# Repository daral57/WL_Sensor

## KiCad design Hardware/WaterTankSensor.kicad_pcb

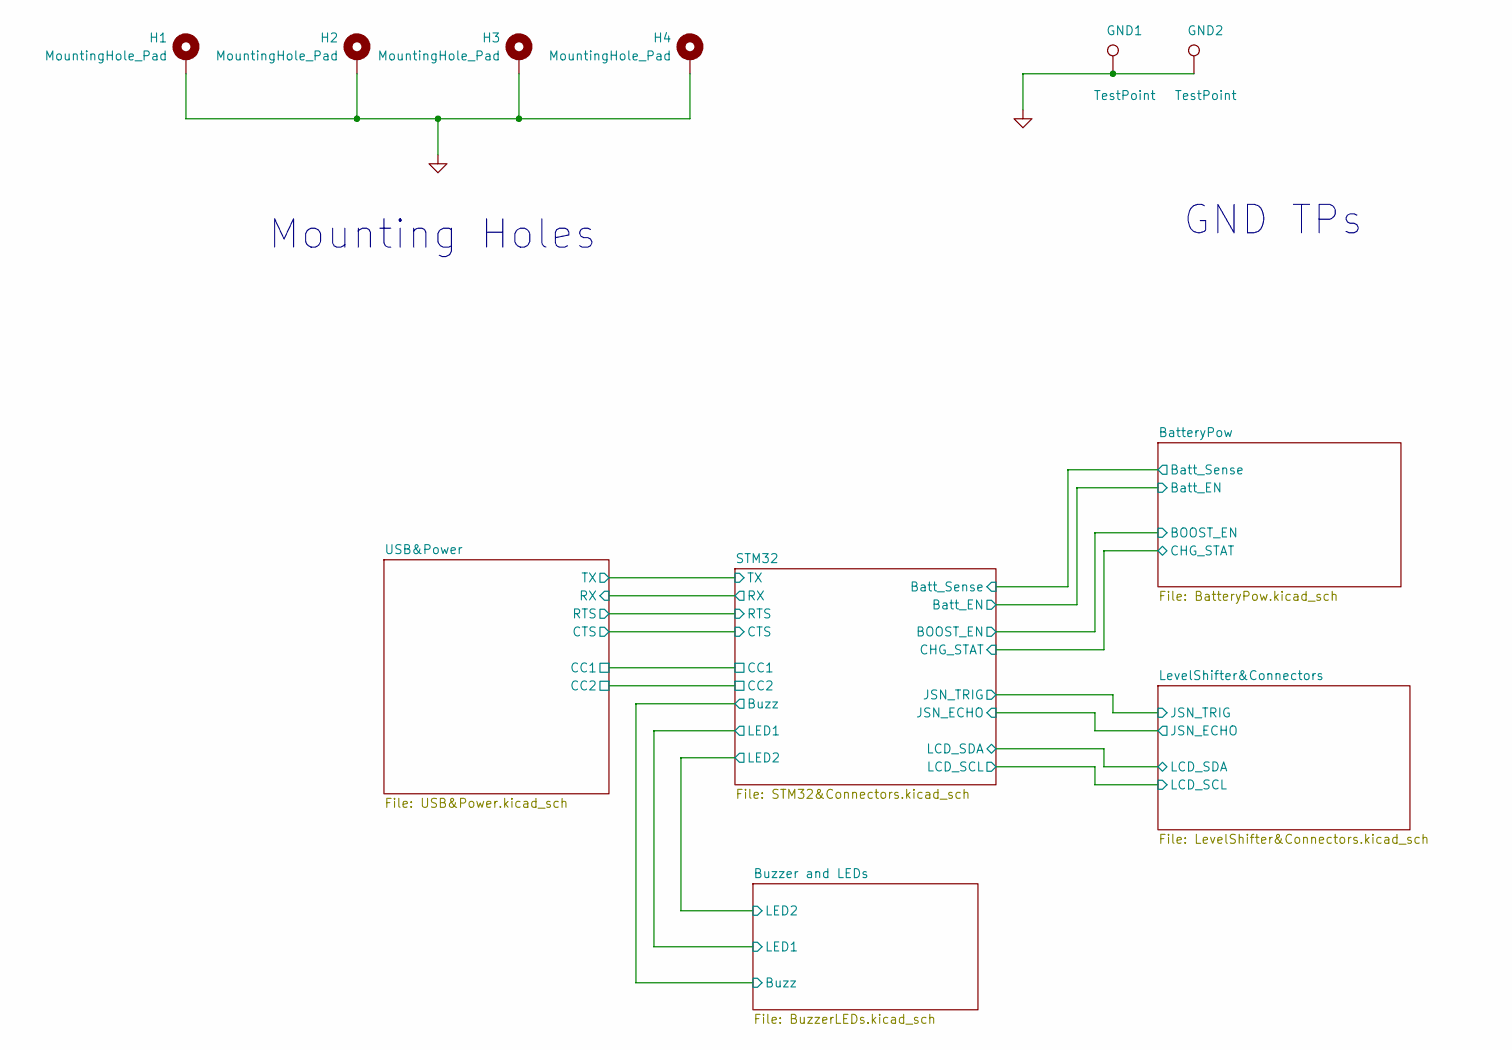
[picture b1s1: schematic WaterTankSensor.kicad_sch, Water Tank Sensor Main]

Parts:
GND1, GND2: TestPoint; TestPoint_Pad_4.0x4.0mm
H1, H2, H3, H4: MountingHole_Pad; MountingHole_3.2mm_M3_Pad_Via

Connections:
GND: GND1.1 (1_1), GND2.1 (1_1), H1.1 (1_1), H2.1 (1_1), H3.1 (1_1), H4.1 (1_1); also elsewhere on the board

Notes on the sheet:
GND TPs
Mounting Holes

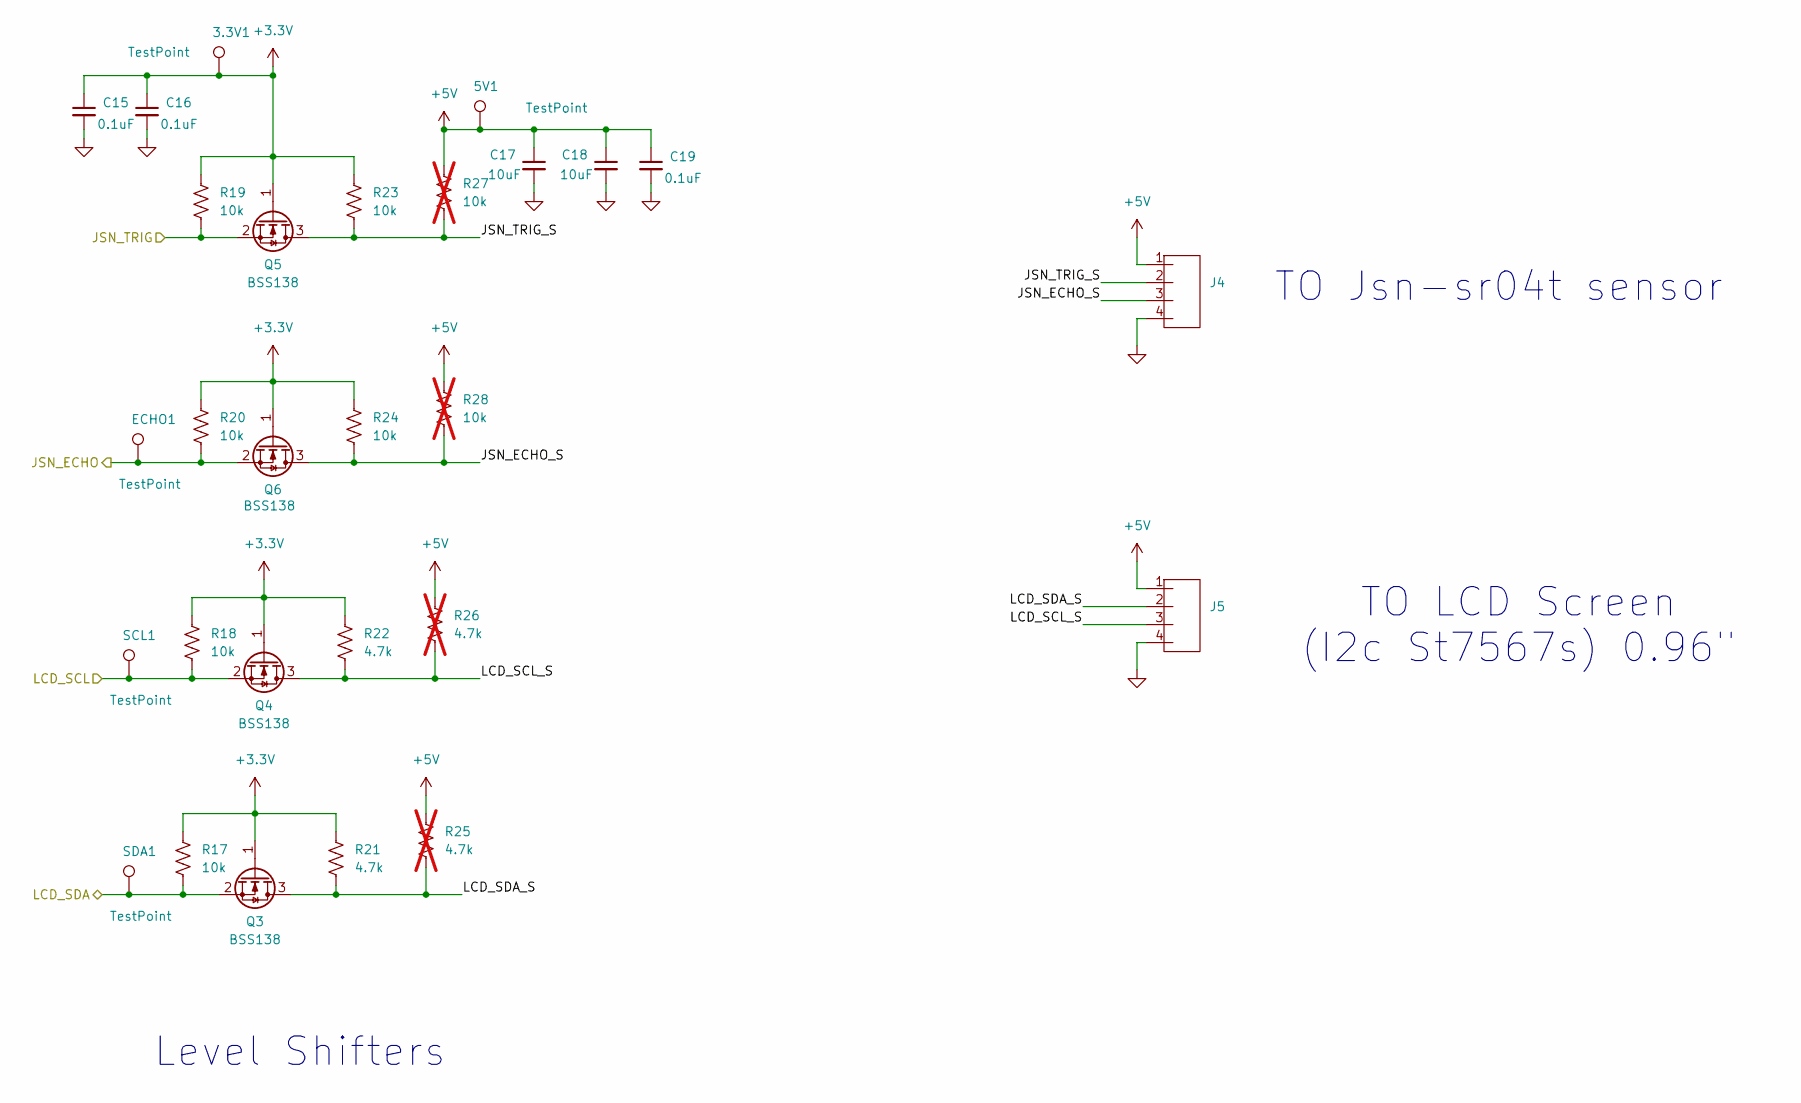
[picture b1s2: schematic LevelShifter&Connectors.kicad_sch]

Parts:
3.3V1, 5V1: TestPoint; TestPoint_Pad_D2.0mm
C15, C16, C19: 0.1uF; C_0603_1608Metric_Pad1.08x0.95mm_HandSolder; MPN CL10B104KO8NNNC
C17, C18: 10uF; C_0603_1608Metric_Pad1.08x0.95mm_HandSolder; MPN CL10B106MQ8NRNC
ECHO1: TestPoint; TestPoint_Pad_D2.0mm
J4, J5: CONN4_A2-4PA-2.54DSA71_HIR; MPN A2-4PA-2.54DSA(71)
Q3, Q4, Q5, Q6: BSS138; SOT-23; MPN BSS138
R17, R18, R19, R20, R23, R24: 10k; R_0603_1608Metric_Pad0.98x0.95mm_HandSolder; MPN CRCW060310K0FKEAHP
R21, R22: 4.7k; R_0603_1608Metric_Pad0.98x0.95mm_HandSolder; MPN CRCW06034K70FKEAHP
R25, R26: 4.7k; R_0603_1608Metric_Pad0.98x0.95mm_HandSolder; MPN CRCW06034K70FKEAHP; not fitted
R27, R28: 10k; R_0603_1608Metric_Pad0.98x0.95mm_HandSolder; MPN CRCW060310K0FKEAHP; not fitted
SCL1: TestPoint; TestPoint_Pad_D2.0mm
SDA1: TestPoint; TestPoint_Pad_D2.0mm

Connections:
+3.3V: 3.3V1.1 (1_1), C15.1, C16.1, Q3.1 (G), Q4.1 (G), Q5.1 (G), Q6.1 (G), R17.2, R18.2, R19.2, R20.2, R21.2, R22.2, R23.2, R24.2; also elsewhere on the board
+5V: 5V1.1 (1_1), C17.1, C18.1, C19.1, J4.1, J5.1, R25.2, R26.2, R27.2, R28.2; also elsewhere on the board
/LevelShifter&Connectors/JSN_ECHO: ECHO1.1 (1_1), Q6.2 (S), R20.1; also elsewhere on the board
/LevelShifter&Connectors/JSN_ECHO_S: J4.3, Q6.3 (D), R24.1, R28.1
/LevelShifter&Connectors/JSN_TRIG: Q5.2 (S), R19.1; also elsewhere on the board
/LevelShifter&Connectors/JSN_TRIG_S: J4.2, Q5.3 (D), R23.1, R27.1
/LevelShifter&Connectors/LCD_SCL: Q4.2 (S), R18.1, SCL1.1 (1_1); also elsewhere on the board
/LevelShifter&Connectors/LCD_SCL_S: J5.3, Q4.3 (D), R22.1, R26.1
/LevelShifter&Connectors/LCD_SDA: Q3.2 (S), R17.1, SDA1.1 (1_1); also elsewhere on the board
/LevelShifter&Connectors/LCD_SDA_S: J5.2, Q3.3 (D), R21.1, R25.1
GND: C15.2, C16.2, C17.2, C18.2, C19.2, J4.4, J5.4; also elsewhere on the board

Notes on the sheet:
TO Jsn-sr04t sensor
TO LCD Screen (I2c St7567s) 0.96"
Level Shifters

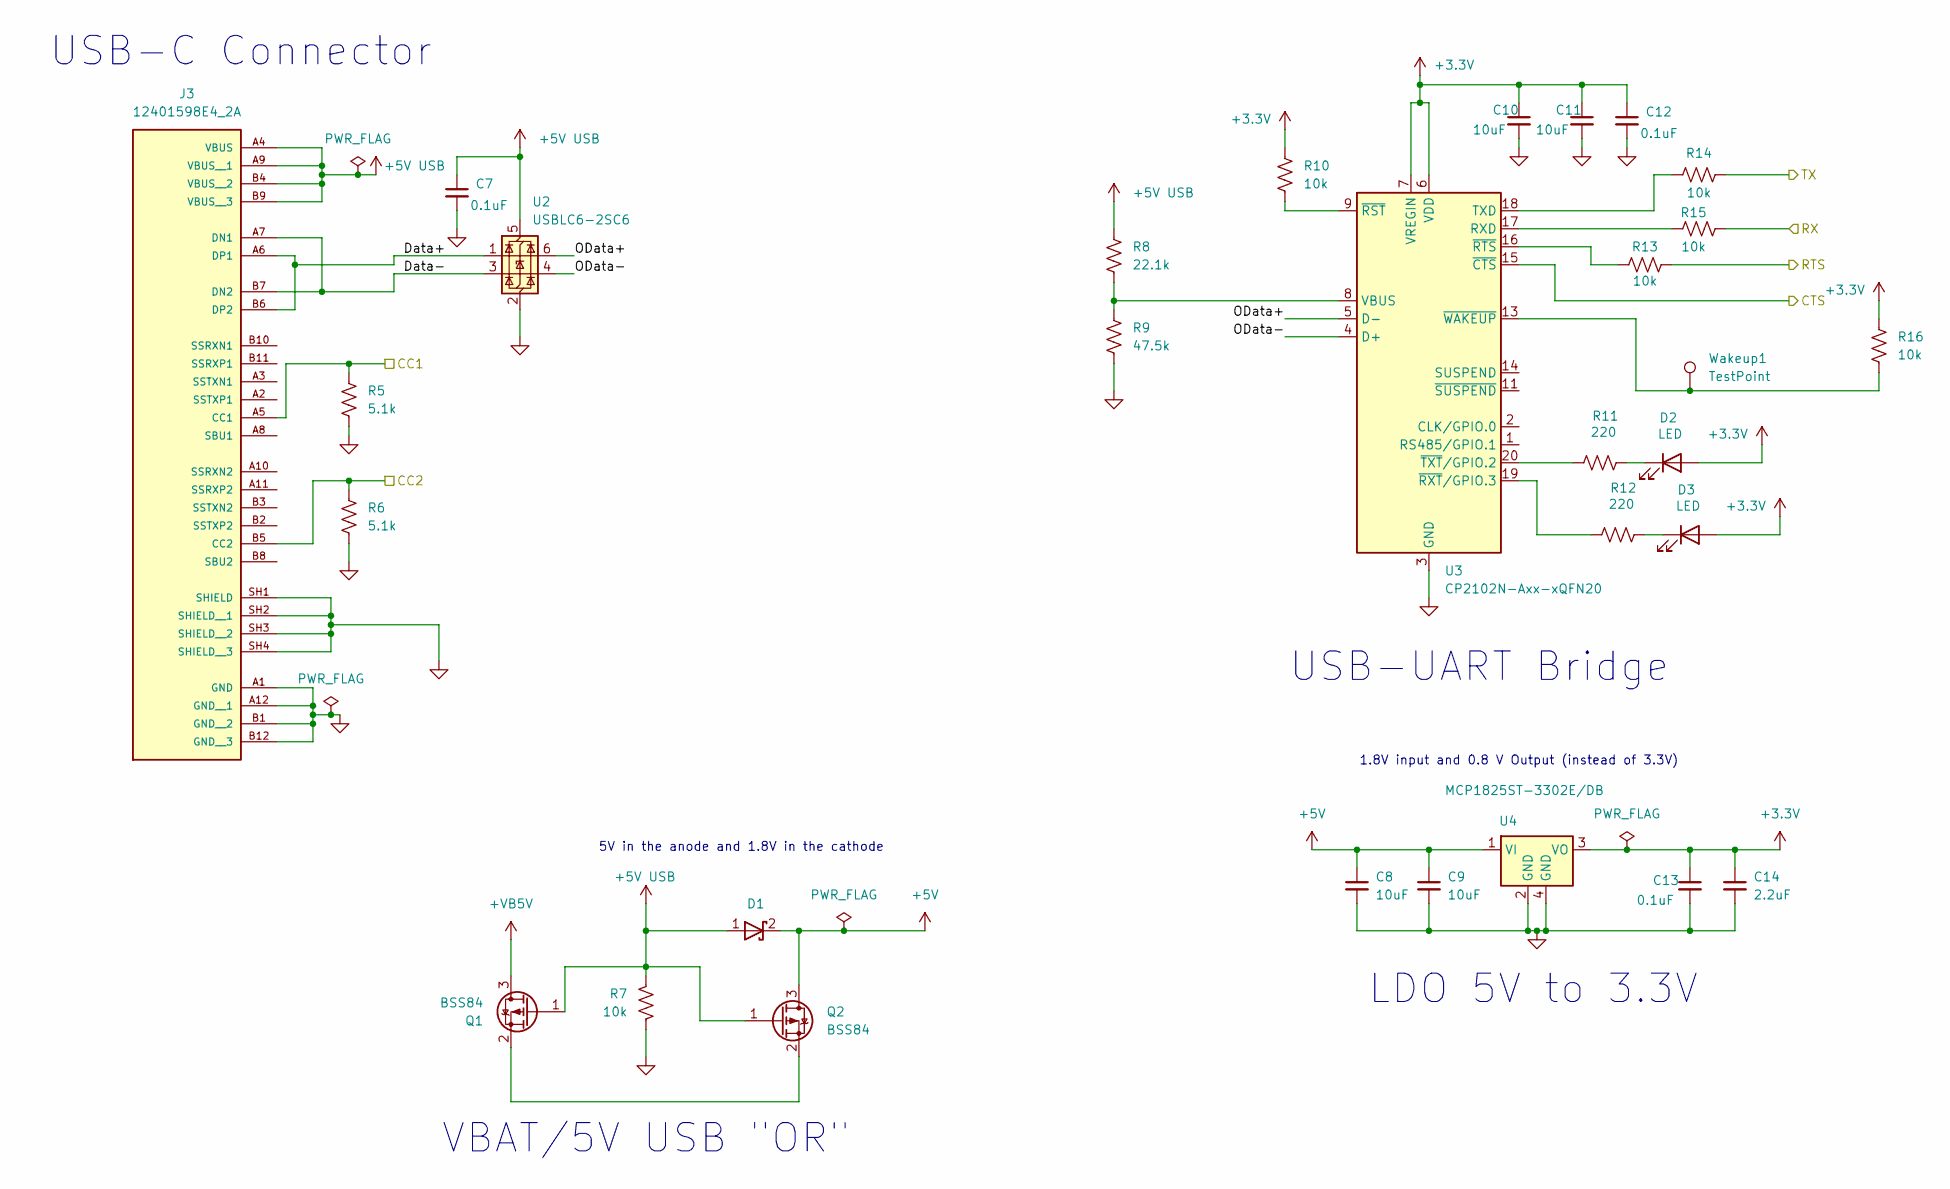
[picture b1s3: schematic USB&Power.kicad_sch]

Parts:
C7, C12, C13: 0.1uF; C_0603_1608Metric_Pad1.08x0.95mm_HandSolder; MPN CL10B104KO8NNNC
C8, C9, C10, C11: 10uF; C_0603_1608Metric_Pad1.08x0.95mm_HandSolder; MPN CL10B106MQ8NRNC
C14: 2.2uF; C_0603_1608Metric_Pad1.08x0.95mm_HandSolder; MPN CL10A225KQ8NNWC
D1: USC_TOS; MPN CUS10S30,H3F
D2, D3: LED; LED_0603_1608Metric; MPN 150060VS75000
J3: 12401598E4_2A; AMPHENOL_12401598E4_2A; PARTREV 4
Q1, Q2: BSS84; SOT-23; MPN BSS84
R5, R6: 5.1k; R_0603_1608Metric_Pad0.98x0.95mm_HandSolder; MPN CRCW0603220RJNEAHP
R7, R10, R13, R15, R16: 10k; R_0603_1608Metric_Pad0.98x0.95mm_HandSolder; MPN CRCW060310K0FKEAHP
R8: 22.1k; R_0603_1608Metric_Pad0.98x0.95mm_HandSolder; MPN CRCW060310K0FKEAHP
R9: 47.5k; R_0603_1608Metric_Pad0.98x0.95mm_HandSolder; MPN CRCW060347K5FKEAHP
R11, R12: 220; R_0603_1608Metric_Pad0.98x0.95mm_HandSolder; MPN CRCW0603220RJNEAHP
R14: 10k; R_0603_1608Metric_Pad0.98x0.95mm_HandSolder; MPN CRCW060322K1FKEAHP
U2: USBLC6-2SC6; SOT-23-6; MPN USBLC6-2SC6
U3: CP2102N-Axx-xQFN20; SiliconLabs_QFN-20-1EP_3x3mm_P0.5mm_EP1.8x1.8mm; MPN CP2102N-A02-GQFN20R
U4: MCP1825ST-3302E/DB; MCP1825ST-3302EDB; MPN MCP1825ST-3302E/DB
Wakeup1: TestPoint; TestPoint_Pad_D2.0mm

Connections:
+3.3V: C10.1, C11.1, C12.1, C13.1, C14.1, D2.2 (A), D3.2 (A), R10.2, R16.2, U3.6 (VDD), U3.7 (VREGIN), U4.3 (VO); also elsewhere on the board
+5V: C8.1, C9.1, D1.2 (K), Q2.3 (D), U4.1 (VI); also elsewhere on the board
+5V USB: C7.1, D1.1 (A), J3.A4 (VBUS), J3.A9 (VBUS__1), J3.B4 (VBUS__2), J3.B9 (VBUS__3), Q1.1 (G), Q2.1 (G), R7.2, R8.1, U2.5 (VBUS); also elsewhere on the board
+VB5V: Q1.3 (D); also elsewhere on the board
/STM32/CC1: J3.A5 (CC1), R5.2; also elsewhere on the board
/STM32/CC2: J3.B5 (CC2), R6.2; also elsewhere on the board
/STM32/NRST: U3.15 (~CTS); also elsewhere on the board
/STM32/RX: R15.1; also elsewhere on the board
/STM32/TCK_SWCLK: R13.1; also elsewhere on the board
/STM32/TX: R14.1; also elsewhere on the board
/USB&Power/Data+: J3.A6 (DP1), J3.B6 (DP2), U2.1 (I/O1)
/USB&Power/Data-: J3.A7 (DN1), J3.B7 (DN2), U2.3 (I/O2)
/USB&Power/OData+: U2.6 (I/O1), U3.5 (D-)
/USB&Power/OData-: U2.4 (I/O2), U3.4 (D+)
GND: C7.2, C8.2, C9.2, C10.2, C11.2, C12.2, C13.2, C14.2, J3.A1 (GND), J3.A12 (GND__1), J3.B1 (GND__2), J3.B12 (GND__3), J3.SH1 (SHIELD), J3.SH2 (SHIELD__1), J3.SH3 (SHIELD__2), J3.SH4 (SHIELD__3), R5.1, R6.1, R7.1, R9.2, U2.2 (GND), U3.3 (GND), U3.12 (GND), U3.21 (GND), U4.2 (GND), U4.4 (GND); also elsewhere on the board
unnamed: D2.1 (K), R11.2
unnamed: D3.1 (K), R12.2
unnamed: Q1.2 (S), Q2.2 (S)
unnamed: R15.2, U3.17 (RXD)
unnamed: R14.2, U3.18 (TXD)
unnamed: R8.2, R9.1, U3.8 (VBUS)
unnamed: R10.1, U3.9 (~RST)
unnamed: R13.2, U3.16 (~RTS)
unnamed: R12.1, U3.19 (~RXT/GPIO.3)
unnamed: R11.1, U3.20 (~TXT/GPIO.2)
unnamed: R16.1, U3.13 (~WAKEUP), Wakeup1.1 (1_1)

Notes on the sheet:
USB-C Connector
VBAT/5V USB "OR"
5V in the anode and 1.8V in the cathode
USB-UART Bridge
LDO 5V to 3.3V
1.8V input and 0.8 V Output (instead of 3.3V)

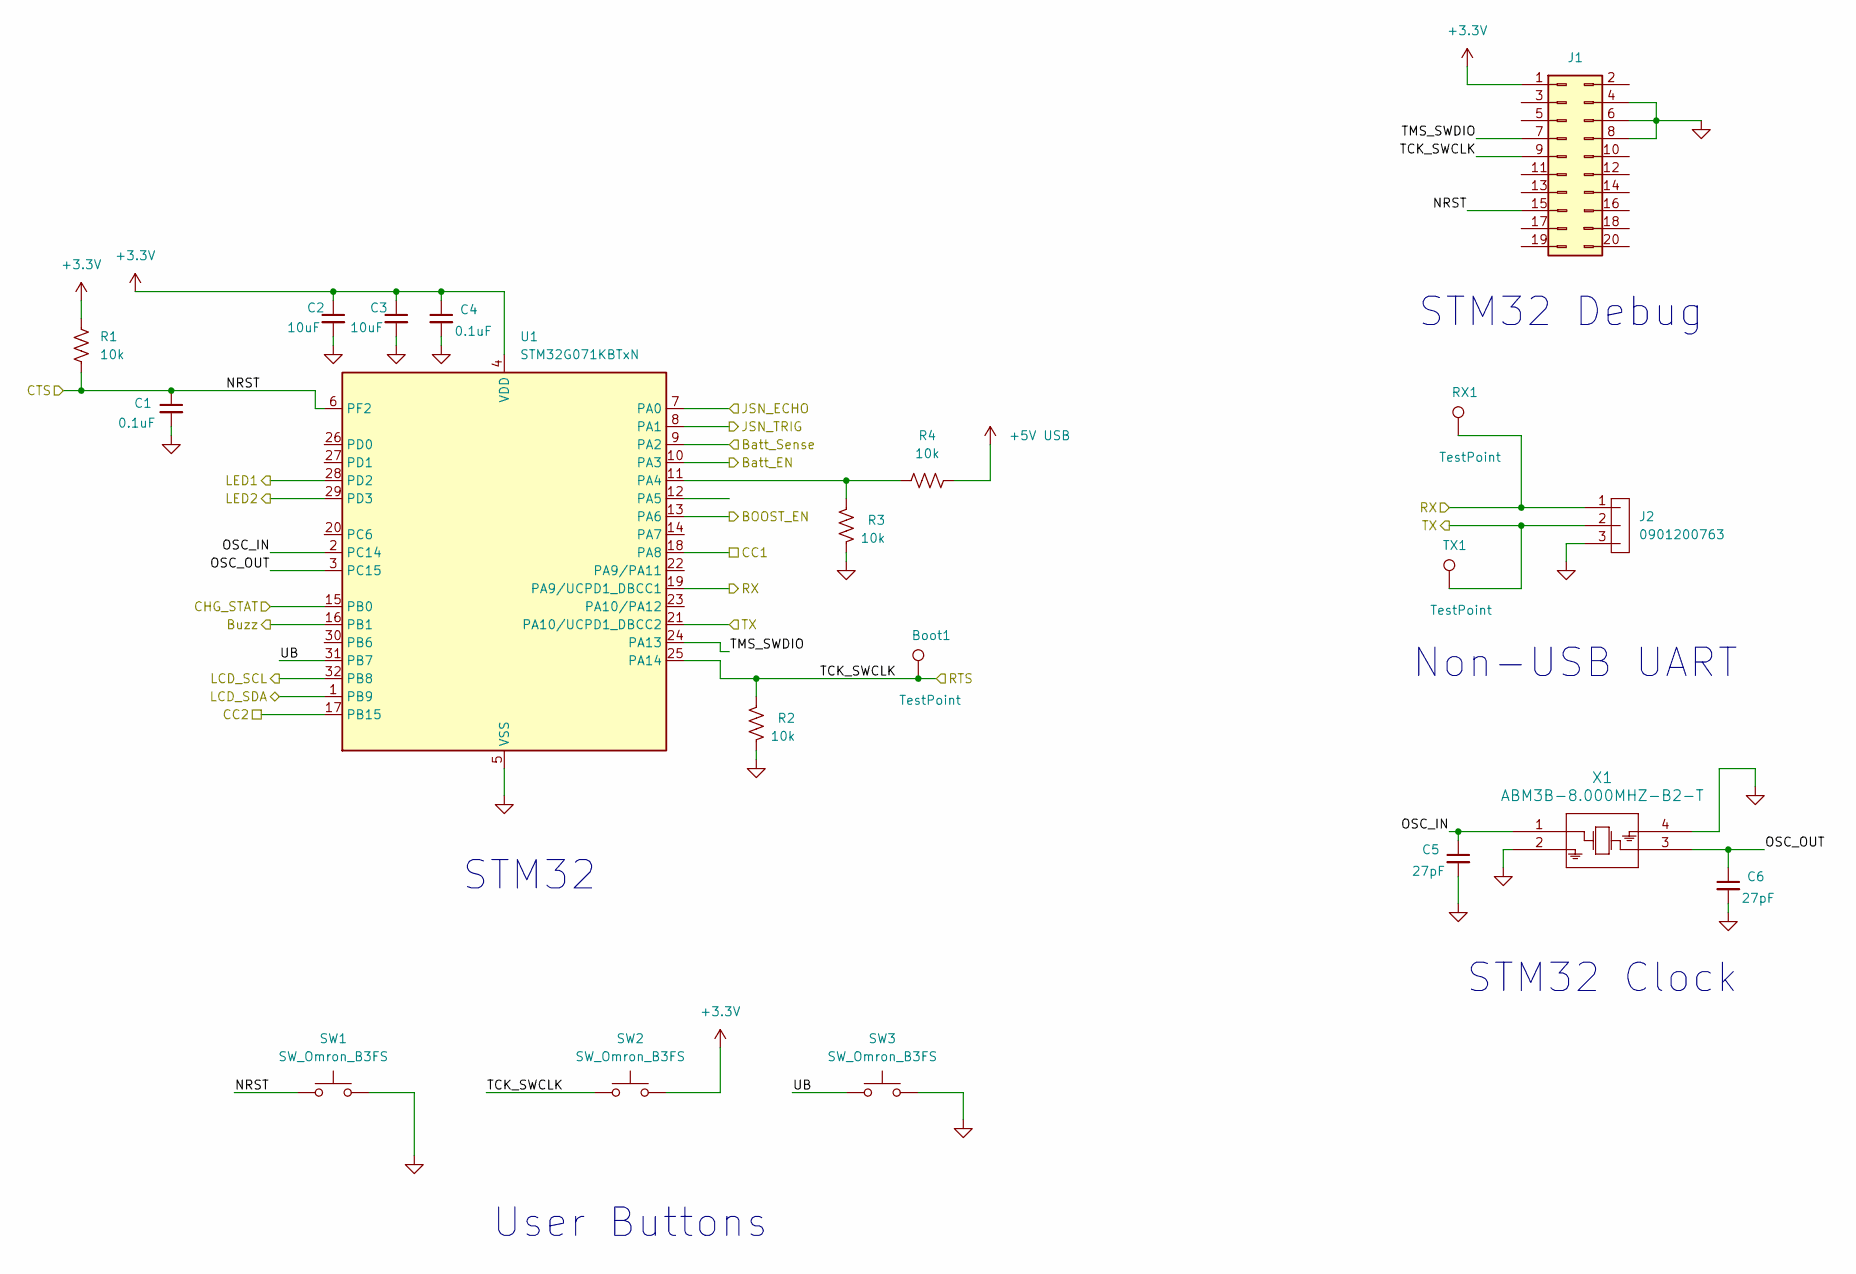
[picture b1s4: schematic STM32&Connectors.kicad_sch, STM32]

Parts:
Boot1: TestPoint; TestPoint_Pad_D2.0mm
C1, C4: 0.1uF; C_0603_1608Metric_Pad1.08x0.95mm_HandSolder; MPN CL10B104KO8NNNC
C2, C3: 10uF; C_0603_1608Metric_Pad1.08x0.95mm_HandSolder; MPN CL10B106MQ8NRNC
C5, C6: 27pF; C_0603_1608Metric_Pad1.08x0.95mm_HandSolder; MPN CL10C270JB8NNNC
J1: 61202021621; MPN 61202021621
J2: 0901200763; CONN_SD-90120-001_03_MOL; MPN 0901200763
R1, R2, R3, R4: 10k; R_0603_1608Metric_Pad0.98x0.95mm_HandSolder; MPN CRCW060310K0FKEAHP
RX1: TestPoint; TestPoint_Pad_D2.0mm
SW1, SW2, SW3: SW_Omron_B3FS; SW_TH_Tactile_Omron_B3F-100x; MPN B3FS-1000P
TX1: TestPoint; TestPoint_Pad_D2.0mm
U1: STM32G071KBTxN; LQFP-32_7x7mm_P0.8mm; MPN STM32G071KBT6N
X1: ABM3B-8.000MHZ-B2-T; ABM3B_ABR; MPN ABM3B-8.000MHZ-B2-T

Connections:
+3.3V: C2.1, C3.1, C4.1, J1.1, R1.1, SW2.2, U1.4 (VDD); also elsewhere on the board
+5V USB: R4.1; also elsewhere on the board
/BatteryPow/BOOST_EN: U1.13 (PA6); also elsewhere on the board
/BatteryPow/Batt_EN: U1.10 (PA3); also elsewhere on the board
/BatteryPow/Batt_Sense: U1.9 (PA2); also elsewhere on the board
/BatteryPow/CHG_STAT: U1.15 (PB0); also elsewhere on the board
/Buzzer and LEDs/Buzz: U1.16 (PB1); also elsewhere on the board
/Buzzer and LEDs/LED1: U1.28 (PD2); also elsewhere on the board
/Buzzer and LEDs/LED2: U1.29 (PD3); also elsewhere on the board
/LevelShifter&Connectors/JSN_ECHO: U1.7 (PA0); also elsewhere on the board
/LevelShifter&Connectors/JSN_TRIG: U1.8 (PA1); also elsewhere on the board
/LevelShifter&Connectors/LCD_SCL: U1.32 (PB8); also elsewhere on the board
/LevelShifter&Connectors/LCD_SDA: U1.1 (PB9); also elsewhere on the board
/STM32/CC1: U1.18 (PA8); also elsewhere on the board
/STM32/CC2: U1.17 (PB15); also elsewhere on the board
/STM32/NRST: C1.1, J1.15, R1.2, SW1.1, U1.6 (PF2); also elsewhere on the board
/STM32/OSC_IN: C5.1, U1.2 (PC14), X1.1
/STM32/OSC_OUT: C6.1, U1.3 (PC15), X1.3
/STM32/RX: J2.1, RX1.1 (1_1), U1.19 (PA9/UCPD1_DBCC1); also elsewhere on the board
/STM32/TCK_SWCLK: Boot1.1 (1_1), J1.9, R2.2, SW2.1, U1.25 (PA14); also elsewhere on the board
/STM32/TMS_SWDIO: J1.7, U1.24 (PA13)
/STM32/TX: J2.2, TX1.1 (1_1), U1.21 (PA10/UCPD1_DBCC2); also elsewhere on the board
/STM32/UB: SW3.1, U1.31 (PB7)
GND: C1.2, C2.2, C3.2, C4.2, C5.2, C6.2, J1.4, J1.6, J1.8, J2.3, R2.1, R3.1, SW1.2, SW3.2, U1.5 (VSS), X1.2, X1.4; also elsewhere on the board
unnamed: R3.2, R4.2, U1.11 (PA4)

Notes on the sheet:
STM32
Non-USB UART
STM32 Debug
User Buttons
STM32 Clock

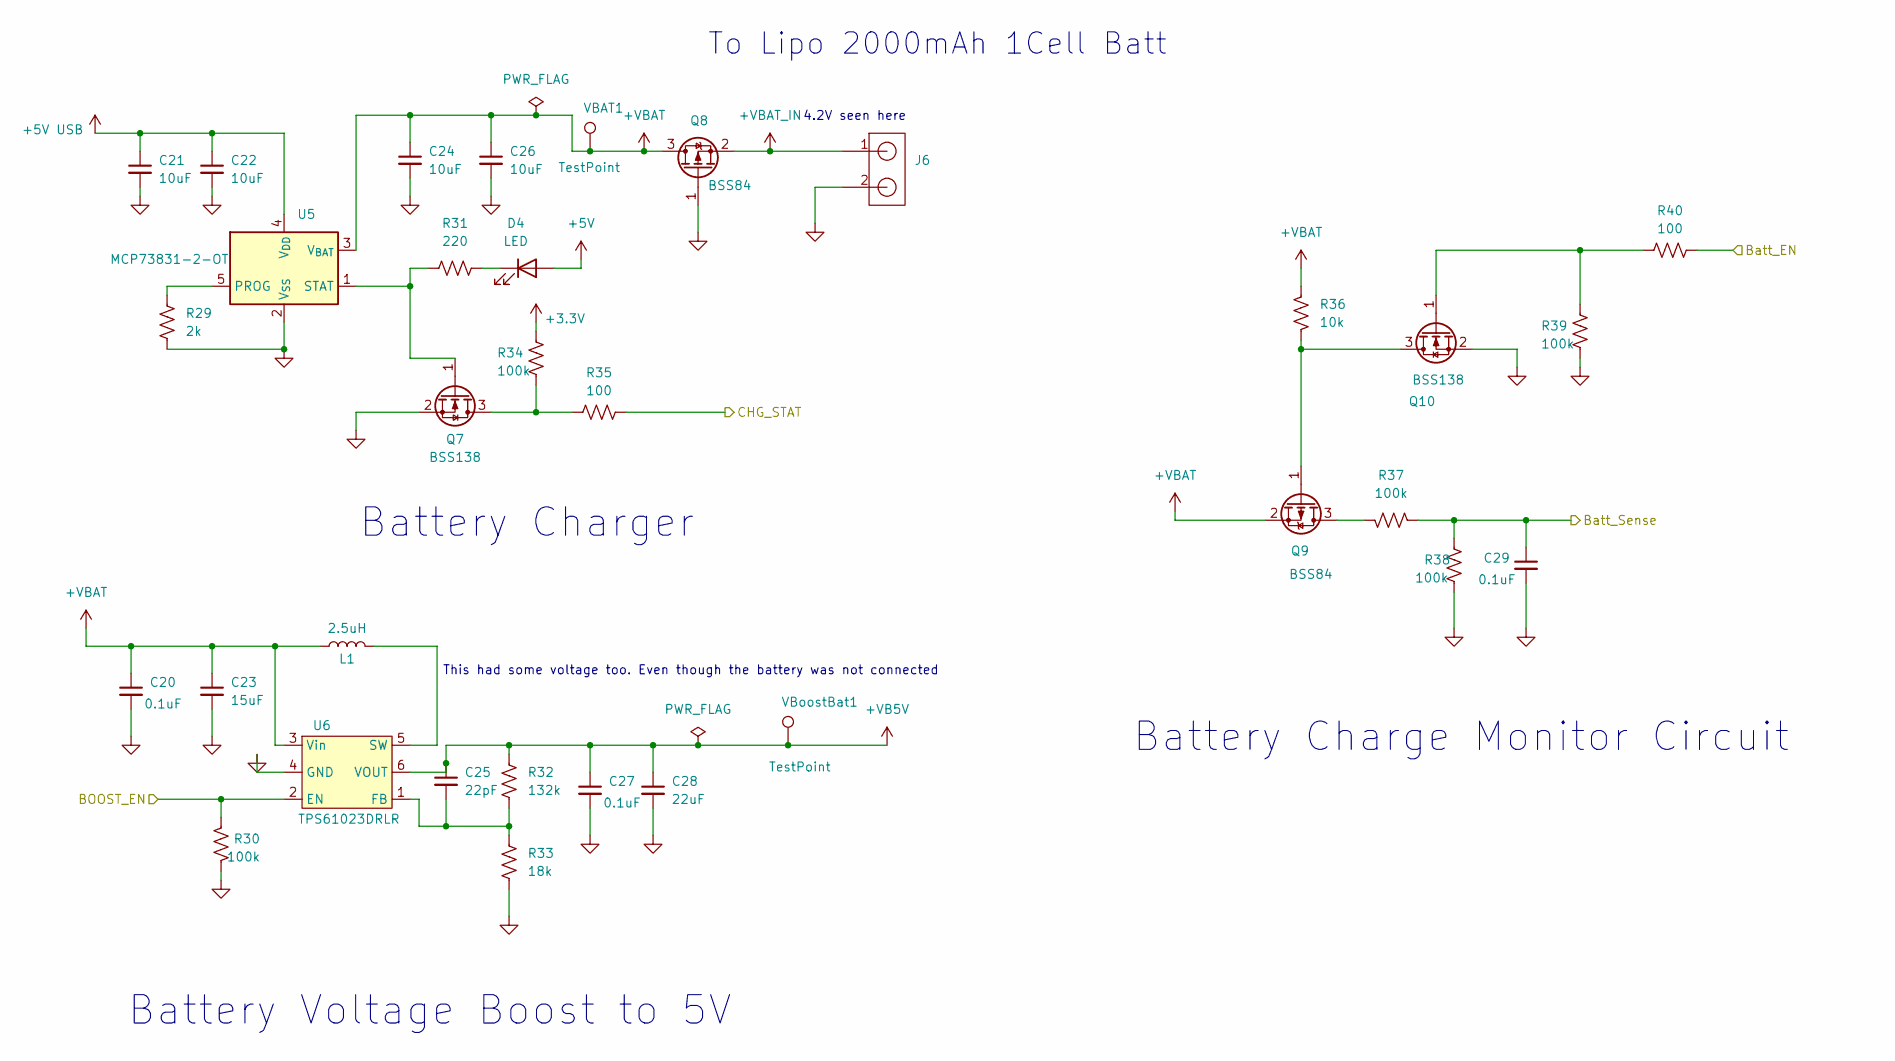
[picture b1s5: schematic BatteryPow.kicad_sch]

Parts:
C20, C27, C29: 0.1uF; C_0603_1608Metric_Pad1.08x0.95mm_HandSolder; MPN CL10B104KO8NNNC
C21, C22, C24, C26: 10uF; C_0603_1608Metric_Pad1.08x0.95mm_HandSolder; MPN CL10B106MQ8NRNC
C23: 15uF; C_1210_3225Metric_Pad1.33x2.70mm_HandSolder; MPN CL32B156KOJVPNE
C25: 22pF; C_0603_1608Metric_Pad1.08x0.95mm_HandSolder; MPN CL10C220JB8NNNC
C28: 22uF; C_1206_3216Metric_Pad1.33x1.80mm_HandSolder; MPN CL31B226MPHNNNE
D4: LED; LED_0603_1608Metric; MPN 150060AS75000
J6: JST_B2B-PH-K-S; MPN B2B-PH-K-S
L1: 2.5uH; L_Bourns_SRR1260; MPN CL31B106MOHNNNE
Q7, Q10: BSS138; SOT-23; MPN BSS138
Q8, Q9: BSS84; SOT-23; MPN BSS84
R29: 2k; R_0603_1608Metric_Pad0.98x0.95mm_HandSolder; MPN CRCW06032K00FKEAHP
R30, R34, R39: 100k; R_0603_1608Metric_Pad0.98x0.95mm_HandSolder; MPN CRCW060310K0FKEAHP
R31: 220; R_0603_1608Metric_Pad0.98x0.95mm_HandSolder; MPN CRCW0603220RJNEAHP
R32: 132k; R_0603_1608Metric_Pad0.98x0.95mm_HandSolder; MPN RT0603DRE07132KL
R33: 18k; R_0603_1608Metric_Pad0.98x0.95mm_HandSolder; MPN CRCW060318K0FKEAHP
R35, R40: 100; R_0603_1608Metric_Pad0.98x0.95mm_HandSolder; MPN CRCW0603100RFKEAHP
R36: 10k; R_0603_1608Metric_Pad0.98x0.95mm_HandSolder; MPN CRCW060310K0FKEAHP
R37, R38: 100k; R_0603_1608Metric_Pad0.98x0.95mm_HandSolder; MPN CRCW0603100KFKEAHP
U5: MCP73831-2-OT; SOT-23-5; MPN MCP73831T-2ACI/OT
U6: TPS61023DRLR; DRL0006A; MPN TPS61023DRLR
VBAT1: TestPoint; TestPoint_Pad_D2.0mm
VBoostBat1: TestPoint; TestPoint_Pad_D2.0mm

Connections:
+3.3V: R34.2; also elsewhere on the board
+5V: D4.2 (A); also elsewhere on the board
+5V USB: C21.1, C22.1, U5.4 (V_{DD}); also elsewhere on the board
+VB5V: C25.1, C27.1, C28.1, R32.2, U6.6 (VOUT), VBoostBat1.1 (1_1); also elsewhere on the board
+VBAT: C20.1, C23.1, C24.1, C26.1, L1.1, Q8.3 (D), Q9.2 (S), R36.1, U5.3 (V_{BAT}), U6.3 (Vin), VBAT1.1 (1_1)
+VBAT_IN: J6.1, Q8.2 (S)
/BatteryPow/BOOST_EN: R30.2, U6.2 (EN); also elsewhere on the board
/BatteryPow/Batt_EN: R40.1; also elsewhere on the board
/BatteryPow/Batt_Sense: C29.1, R37.2, R38.2; also elsewhere on the board
/BatteryPow/CHG_STAT: R35.1; also elsewhere on the board
GND: C20.2, C21.2, C22.2, C23.2, C24.2, C26.2, C27.2, C28.2, C29.2, J6.2, Q7.2 (S), Q8.1 (G), Q10.2 (S), R29.2, R30.1, R33.1, R38.1, R39.1, U5.2 (V_{SS}), U6.4 (GND); also elsewhere on the board
unnamed: D4.1 (K), R31.2
unnamed: Q7.3 (D), R34.1, R35.2
unnamed: Q7.1 (G), R31.1, U5.1 (STAT)
unnamed: Q9.3 (D), R37.1
unnamed: Q9.1 (G), Q10.3 (D), R36.2
unnamed: Q10.1 (G), R39.2, R40.2
unnamed: R29.1, U5.5 (PROG)
unnamed: C25.2, R32.1, R33.2, U6.1 (FB)
unnamed: L1.2, U6.5 (SW)

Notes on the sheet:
Battery Voltage Boost to 5V
To Lipo 2000mAh 1Cell Batt
Battery Charger
Battery Charge Monitor Circuit
This had some voltage too. Even though the battery was not connected
4.2V seen here

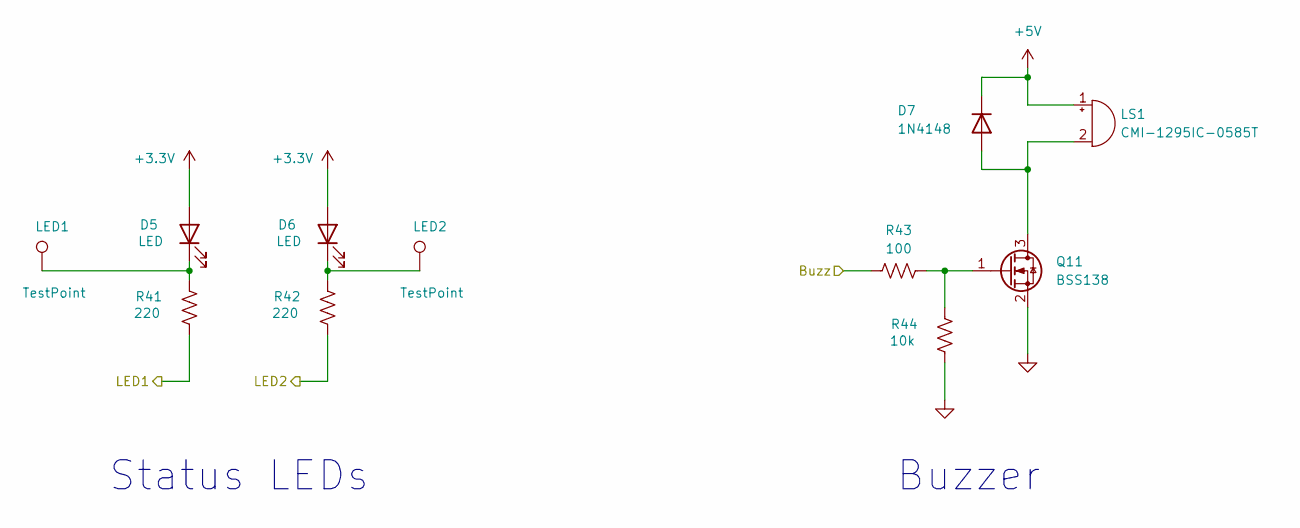
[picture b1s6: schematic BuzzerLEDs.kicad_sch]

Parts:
D5: LED; LED_0603_1608Metric; MPN 150060VS75000
D6: LED; LED_0603_1608Metric; MPN 150060SS75000
D7: 1N4148; D_SOD-123; MPN 1N4148W
LED1, LED2: TestPoint; TestPoint_Pad_D2.0mm
LS1: CMI-1295IC-0585T; CUI_CMI-1295IC-0585T; MPN CMI-1295IC-0585T
Q11: BSS138; SOT-23; MPN BSS138
R41, R42: 220; R_0603_1608Metric_Pad0.98x0.95mm_HandSolder; MPN CRCW0603220RJNEAHP
R43: 100; R_0603_1608Metric_Pad0.98x0.95mm_HandSolder; MPN CRCW0603100RFKEAHP
R44: 10k; R_0603_1608Metric_Pad0.98x0.95mm_HandSolder; MPN CRCW060310K0FKEAHP

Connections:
+3.3V: D5.2 (A), D6.2 (A); also elsewhere on the board
+5V: D7.1 (K), LS1.1 (+); also elsewhere on the board
/Buzzer and LEDs/Buzz: R43.2; also elsewhere on the board
/Buzzer and LEDs/LED1: R41.1; also elsewhere on the board
/Buzzer and LEDs/LED2: R42.1; also elsewhere on the board
GND: Q11.2 (S), R44.1; also elsewhere on the board
unnamed: D5.1 (K), LED1.1 (1_1), R41.2
unnamed: D6.1 (K), LED2.1 (1_1), R42.2
unnamed: D7.2 (A), LS1.2 (-), Q11.3 (D)
unnamed: Q11.1 (G), R43.1, R44.2

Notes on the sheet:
Buzzer
Status LEDs

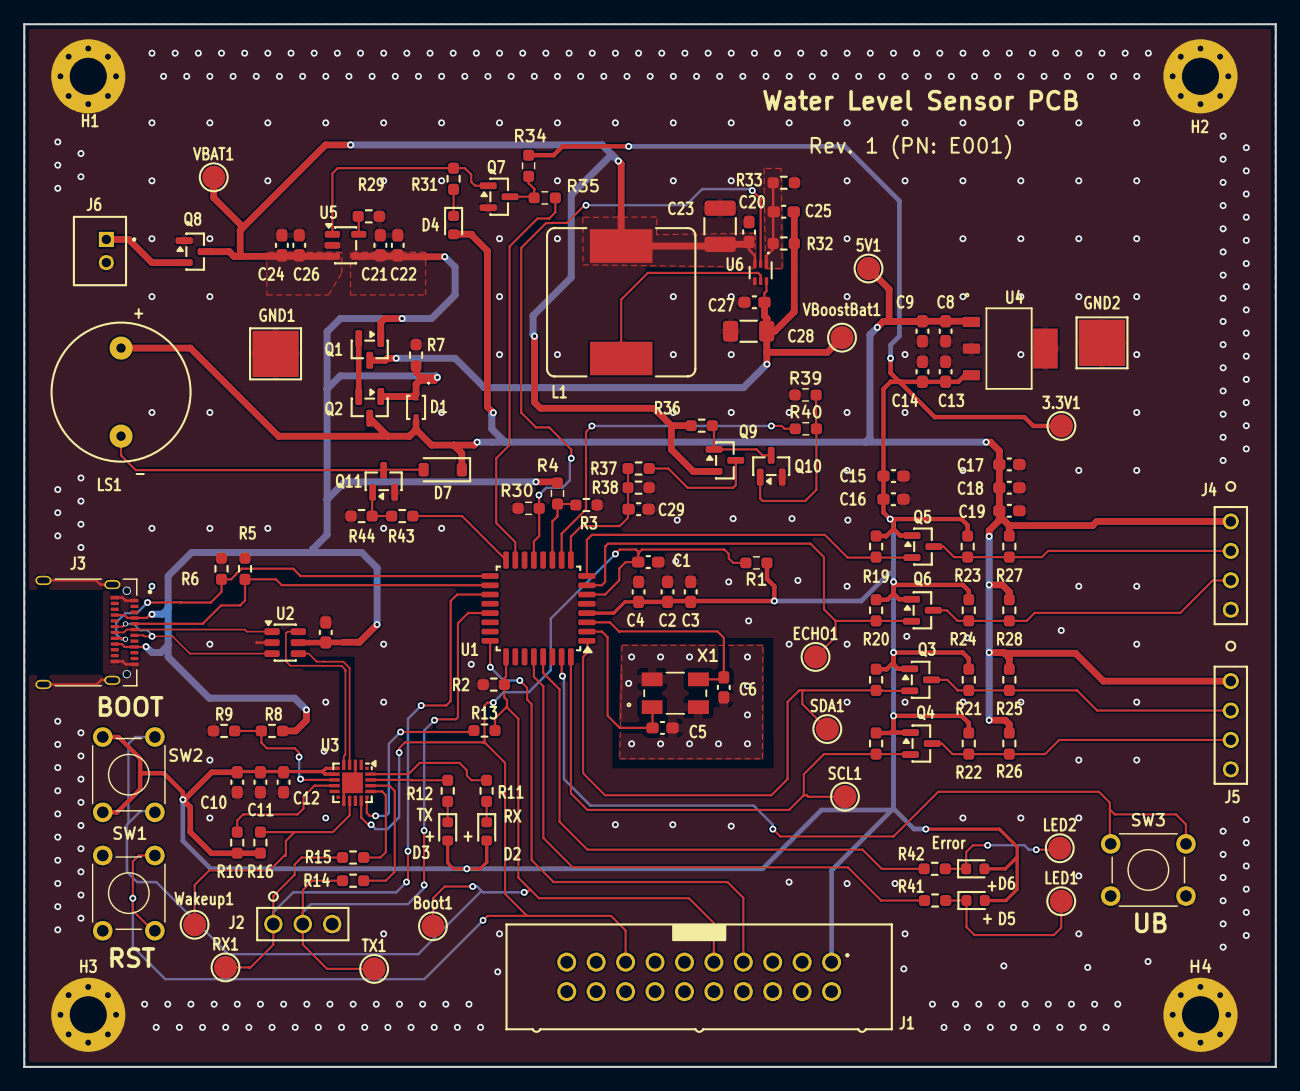
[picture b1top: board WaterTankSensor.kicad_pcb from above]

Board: 4 copper layers, 108.0 x 90.0 mm, 128 parts (0 on the bottom side), 61 nets.

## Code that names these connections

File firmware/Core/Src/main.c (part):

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
    // --- MODER: Set pin modes ---
    // First clear all pins we're configuring, then set their mode.
    // PA0  = Alternate Function (10) → Timer input capture
    // PA1  = Output (01)             → JSN_TRIG
    // PA2  = Analog (11)             → Batt_Sense ADC
    // PA3  = Output (01)             → Batt_EN
    // PA4  = Analog (11)             → USB_5V_Sense ADC
    // PA6  = Output (01)             → BOOST_EN
    // PA8  = Analog (11)             → CC1 ADC
    // PA9  = Alternate Function (10) → USART1_TX
    // PA10 = Alternate Function (10) → USART1_RX
    // PA13 = Alternate Function (10) → SWDIO  (default, just leave it)
    // PA14 = Alternate Function (10) → SWCLK  (default, just leave it)


    GPIOA->ODR &= ~( (1U << 1)   // PA1 JSN_TRIG  → LOW
               | (1U << 3)   // PA3 BATT_EN   → LOW
               | (1U << 6)); // PA6 BOOST_EN  → LOW

    // Clear the bits for PA0-PA10 (PA13/PA14 left as default AF)
    GPIOA->MODER &= ~( (3U << (0  * 2))    // PA0
                     | (3U << (1  * 2))    // PA1
                     | (3U << (2  * 2))    // PA2
                     | (3U << (3  * 2))    // PA3
                     | (3U << (4  * 2))    // PA4
                     | (3U << (6  * 2))    // PA6
                     | (3U << (9  * 2))    // PA9
                     | (3U << (10 * 2)) ); // PA10

    // Now set the modes
    GPIOA->MODER |=  ( (2U << (0  * 2))    // PA0  = AF
                     | (1U << (1  * 2))    // PA1  = Output
                     | (3U << (2  * 2))    // PA2  = Analog
                     | (1U << (3  * 2))    // PA3  = Output
                     | (3U << (4  * 2))    // PA4  = Analog
                     | (1U << (6  * 2))    // PA6  = Output
                     | (2U << (9  * 2))    // PA9  = AF (USART1_TX)
                     | (2U << (10 * 2)) ); // PA10 = AF (USART1_RX)

    // --- OTYPER: All outputs Push-Pull (default 0, nothing to set) ---

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
    // --- OSPEEDR: Low speed for all (default 0, nothing to set) ---

    // --- Alternate Function: PA0 → TIM2_CH1, PA9/PA10 → USART1 ---
    // AFR[0] covers PA0-PA7, AFR[1] covers PA8-PA15
    // PA0  → AF2 (TIM2_CH1)
    // PA9  → AF1 (USART1_TX)
    // PA10 → AF1 (USART1_RX)
    GPIOA->AFR[0] &= ~(0xFU << (0 * 4));    // Clear PA0 AF bits            
    GPIOA->AFR[0] |=  ( (2U << (0 * 4)) );   // PA0 = AF2 (TIM2_CH1)

    GPIOA->AFR[1] &= ~( (0xFU << ((9-8)  * 4))   // Clear PA9  AF bits
                      | (0xFU << ((10-8) * 4)) ); // Clear PA10 AF bits

    GPIOA->AFR[1] |=  ( (1U << ((9-8)  * 4))     // PA9  = AF1 (USART1_TX)
                      | (1U << ((10-8) * 4)) );   // PA10 = AF1 (USART1_RX)


    // =========================================================
    // GPIOB CONFIGURATION
    // =========================================================

    // PB0  = Input                                          → CHG_STAT
    // PB1  = Alternate Function (10)                        → PWM Buzz
    // PB8  = Alternate Function (10)                        → I2C1_SCL
    // PB9  = Alternate Function (10)                        → I2C1_SDA
    // PB15 = Analog (11)                                    → CC2 ADC

    GPIOB->MODER &= ~( (3U << (0  * 2))    // PB0
                     | (3U << (1  * 2))    // PB1
                     | (3U << (8  * 2))    // PB8
                     | (3U << (9  * 2)) );  // PB9


    GPIOB->MODER |=  ( (0U << (0  * 2))    // PB0  = Input
                     | (2U << (1  * 2))    // PB1  = AF (PWM)
                     | (2U << (8  * 2))    // PB8  = AF (I2C1_SCL)
                     | (2U << (9  * 2)) ); // PB9  = AF (I2C1_SDA) 

    // OTYPER: PB8 and PB9 open-drain (I2C requires it!)
    GPIOB->OTYPER  |= ((1U << 8)             // PB8  = Open-Drain (I2C)
                   | (1U << 9));            // PB9  = Open-Drain (I2C)

    // PUPDR: PB8 and PB9 pull-up (I2C requires it!)
    GPIOB->PUPDR &= ~( (3U << (0  * 2)) 
                     | (3U << (8 * 2))
                     | (3U << (9 * 2)) );
    GPIOB->PUPDR |=  ( (1U << (0  * 2))    // PB0 = Pull-Up
                     | (1U << (8 * 2))     // PB8 = Pull-Up
                     | (1U << (9 * 2)) );  // PB9 = Pull-Up

    // Alternate Functions:
    // PB1  → AF0 (TIM14_CH1)
    // PB8  → AF6 (I2C1_SCL)
    // PB9  → AF6 (I2C1_SDA)
    GPIOB->AFR[0] &= ~(0xFU << (1 * 4));  // Clear PB1 AF bits and sets to AF0 (TIM14_CH1)

    GPIOB->AFR[1] &= ~( (0xFU << ((8-8) * 4))
                      | (0xFU << ((9-8) * 4)) );
    GPIOB->AFR[1] |=  ( (6U << ((8-8) * 4))   // PB8 = AF6 (I2C1_SCL)
                      | (6U << ((9-8) * 4)) ); // PB9 = AF6 (I2C1_SDA)


    // =========================================================
    // GPIOD CONFIGURATION
    // =========================================================

    GPIOD->ODR &= ~( (1U << 2)   // PD2 LED1 → OFF
               | (1U << 3)); // PD3 LED2 → OFF

    // PD2 = Output (01) → LED1
    // PD3 = Output (01) → LED2

    GPIOD->MODER &= ~( (3U << (2 * 2))
                     | (3U << (3 * 2)) );

    GPIOD->MODER |=  ( (1U << (2 * 2))    // PD2 = Output
                     | (1U << (3 * 2)) );  // PD3 = Output

    // OTYPER: LEDS are Open-Drain by design 
    GPIOD->OTYPER  |= ( (1U << 2)             // PD2  = Open-Drain (LED)
                    | (1U << 3));            // PD3  = Open-Drain (LED)
    // PUPDR: No pull resistors (default, nothing to set)
    // OSPEEDR: Low speed (default, nothing to set)
}
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
    // 4. Configure CH1 as Input Capture
    // CCMR1 controls channels 1 and 2
    // CC1S = 01 → CH1 is input, mapped to TI1 (PA0)
    TIM2->CCMR1 &= ~TIM_CCMR1_CC1S;        // Clear CC1S bits
    TIM2->CCMR1 |=  (1U << TIM_CCMR1_CC1S_Pos); // CC1S = 01 (input on TI1)

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    uint32_t start, end, pulse_width;

    // Step 1 — Send 10µs trigger pulse
    GPIOA->ODR |=  (1U << 1);   // PA1 HIGH
    delay_us(10);                // Wait 10µs
    GPIOA->ODR &= ~(1U << 1);   // PA1 LOW

 uint32_t timeout = 100000;
    while (!(TIM2->SR & TIM_SR_CC1IF)) {
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// Read battery voltage in millivolts
// Adjust divider_ratio to match your schematic
uint32_t Batt_ReadmV(void) {
    uint16_t raw = ADC_Read(2);          // PA2 = channel 2
    uint32_t mv  = ADC_ToMillivolts(raw);

    // Correct for voltage divider
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
// Read USB 5V sense in millivolts
uint32_t USB_ReadmV(void) {
    uint16_t raw = ADC_Read(4);          // PA4 = channel 4
    uint32_t mv  = ADC_ToMillivolts(raw);

    // Correct for voltage divider
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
